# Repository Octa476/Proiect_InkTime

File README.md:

# Proiect_InkTime

Schematic, PCB design si 3D modeling pentru ceasul InkTime in cadrul proiectului de la materia TSC.

## Diagrama Bloc

Diagrama bloc a proietului (o varianta destul de minimala, dar suficienta pentru a intelege cum interactioneaza componentele intre ele) este prezenta in folder-ul root proiectului in varianta HTML si a fost realizata folosind [www.drawio.com](https://www.drawio.com/).

## BOM
Un Bills of Materials cu componentele folosite in cadrul acestui proiect.

### Componente active
 
| Component | Part Number | Package | Function | JLCPCB Part | Datasheet |
|-----------|------------|---------|----------|-------------|-----------|
| MCU | nRF52840-QIAA-R | aQFN73 (7x7) | Microcontroller + BLE + USB | [C190794](https://jlcpcb.com/partdetail/Nordic_Semicon-NRF52840_QIAA_R/C190794) | [Datasheet](https://infocenter.nordicsemi.com/pdf/nRF52840_PS_v1.8.pdf) |
| Charger / Power Path | BQ25180YBGR | DSBGA-8 | Li-Ion/LiPo charger with power path | [C3682423](https://jlcpcb.com/partdetail/TexasInstruments-BQ25180YBGR/C3682423) | [Datasheet](https://www.ti.com/lit/ds/symlink/bq25180.pdf) |
| Buck-Boost Regulator | RT6160AWSC | WLCSP-15 | 3.3V system rail regulator | [C7065276](https://jlcpcb.com/partdetail/Richtek_Tech-RT6160AWSC/C7065276) | [Datasheet](https://www.richtek.com/assets/product_file/RT6160A/DS6160A-05.pdf) |
| Fuel Gauge | MAX17048G+T10 | DFN-8 (2x2) | Battery SOC monitoring | [C2682616](https://jlcpcb.com/partdetail/AnalogDevices-MAX17048G_T10/C2682616) | [Datasheet](https://www.analog.com/media/en/technical-documentation/data-sheets/MAX17048-MAX17049.pdf) |
| Accelerometer | BMA421 | LGA-12 (2x2) | Step counting + motion wake | [C5242966](https://jlcpcb.com/partdetail/Bosch_Sensortec-BMA421/C5242966) | [Datasheet](https://www.bosch-sensortec.com/media/boschsensortec/downloads/datasheets/bst-bma421-ds004.pdf) |
| Haptic Driver | DRV2605LDGSR | VSSOP-10 | ERM motor driver with effects library | [C527464](https://jlcpcb.com/partdetail/TexasInstruments-DRV2605LDGSR/C527464) | [Datasheet](https://www.ti.com/lit/ds/symlink/drv2605l.pdf) |
| PFET (EPD power) | SI2301CDS | SOT-23 | E-paper display power gating | [C10487](https://jlcpcb.com/partdetail/Changjiang_Electronics_Tech_CJ-SI2301CDS/C10487) | [Datasheet](https://www.vishay.com/docs/68749/si2301cds.pdf) |
| USB ESD Protection | USBLC6-2SC6Y | SOT-23-6 | ESD protection on USB data lines | [C7519](https://jlcpcb.com/partdetail/Stmicroelectronics-USBLC6_2SC6Y/C7519) | [Datasheet](https://www.st.com/resource/en/datasheet/usblc6-2.pdf) |
 
### Conectori & Componente electromecanice
 
| Component | Part Number | Package | Function | JLCPCB Part | Datasheet |
|-----------|------------|---------|----------|-------------|-----------|
| FPC Connector (Display) | Molex 503480-2400 | 24-pin 0.5mm FPC | E-paper display FPC connection | [C2857160](https://jlcpcb.com/partdetail/Molex-5034802400/C2857160) | [Datasheet](https://www.molex.com/en-us/products/part-detail/5034802400) |
| USB Type-C Connector | KH-TYPE-C-16P | 16-pin SMD | USB charging + data | [C2765186](https://jlcpcb.com/partdetail/Kinghelm-KH_TYPE_C_16P/C2765186) | [Datasheet](https://datasheet.lcsc.com/lcsc/2012121836_Kinghelm-KH-TYPE-C-16P_C2765186.pdf) |
| Buttons (x3) | EVP-AKE31A | SMD tactile | Up / Down / Enter navigation | [C2845028](https://jlcpcb.com/partdetail/Panasonic-EVP_AKE31A/C2845028) | [Datasheet](https://industrial.panasonic.com/cdbs/www-data/pdf/ATV0000/ATV0000CE3.pdf) |
| SWD Debug Header | TC2030-IDC | Tag-Connect 6-pin | SWD programming + debug | - | [Datasheet](https://4donline.ihs.com/images/VipMasterIC/IC/TGCN/TGCN-S-A0008988129/TGCN-S-A0008988129-1.pdf?hkey=61A2E4C270F0397D049F8F05BD4F1054) |
| Antenna | 2450AT18B100E | SMD 3216 | 2.4 GHz BLE chip antenna | [C5179427](https://jlcpcb.com/partdetail/Johanson_Technology-2450AT18B100E/C5179427) | [Datasheet](https://www.johansontechnology.com/datasheets/2450AT18B100/2450AT18B100.pdf) |
 
### Componente Pasive
 
| Component | Value | Package | Qty | Function |
|-----------|-------|---------|-----|----------|
| Capacitors (EPD) | 1uF/50V | 0402 | 9 | E-paper driver capacitors |
| Capacitors (decoupling) | 100nF | 0201 | 5 | MCU + peripheral decoupling |
| Capacitors (crystal load) | 12pF | 0201 | 4 | 32MHz + 32.768kHz crystal loads |
| Capacitors (bulk) | 4.7uF | 0402 | 4 | MCU power rail bulk decoupling |
| Capacitors (charger) | 1uF | 0402 | 3 | BQ25180 CIN/CSYS/CBAT |
| Capacitors (power) | 22uF | 0402 | 2 | RT6160 input capacitors |
| Capacitors (USB) | 4.7uF | 0402 | 1 | DECUSB capacitor |
| Resistors (I2C pull-up) | 10k | 0201 | 2 | I2C SDA/SCL pull-ups |
| Resistors (USB CC) | 5.1k | 0201 | 2 | USB Type-C CC1/CC2 pull-downs |
| Inductor (DC/DC) | 10uH | 0402 | 1 | nRF52840 REG1 DC/DC inductor |
| Inductor (buck-boost) | 0.47uH | 2012 | 1 | RT6160 power stage inductor |
| Crystal | 32 MHz | 2016 | 1 | HFXO for MCU + radio |
| Crystal | 32.768 kHz | 3215 | 1 | LFXO for RTC timekeeping |
 
### Componente asamblate manual
 
| Component | Description | Datasheet |
|-----------|-------------|-----------|
| E-Paper Display | 1.54" 200x200 e-paper panel (connected via 24-pin FPC) | [Datasheet](https://www.tme.eu/Document/0ca57a8ffbcd57b5bca53252eb9d6ec3/WSH-12561.pdf)
| LiPo Battery | 3.7V / 250mAh lithium polymer cell | [Datasheet](https://www.tme.eu/Document/b9e12bf26ad0ba929a22ab5d58f022cd/AKY0106.pdf) |
| ERM Motor | Vibration motor (LCM1027B3605F, wire-soldered) | [Datasheet](https://www.mouser.com/pdfDocs/ProductOverview_DFRobot-FIT0774.pdf?srsltid=AfmBOorF7wbF3rhjcccF6FYMm4IWaUvm-yoIZHtvcCPKd2GPxZIuuKFv) |
| Case | 3D-printed case (SLS/MJF or FDM prototype) | [Soon](https://www.youtube.com/watch?v=xm3YgoEiEDc&list=RDxm3YgoEiEDc&start_radio=1) |

## Descrierea functionalitatii hardware

### **I2C**: LiPo Charger, DC/DC, IMU, Fuel Gauge, Haptic Driver;
### **SPI**: E-Paper Display Connector;

### Sheet1:
- **LiPo Charger** este folosit pentru a incarca bateria;
- **DC/DC** este un stabilizator de tensiune si este folosit pentru a oferi o tensiune stabila de 3V3 intregii placi;
- **IMU** este un accelerometru, fiind utilizat pentru determinarea acceleratiei pe cele 3 axe, numararea pasilor, etc;
- **nRF52840** este microcontroller-ul placutei si controleaza si orchestreaza intreaga functionalitate a acesteia;
- **SWD** - este mufa pentru conectorul de debug;

### Sheet2:
- **E-Paper Drive Circuit** este folosit pentru a controla display-ul si a oferii tensiuni de alimentare potrivite;
- **E-Paper Display Connector** - conectorul ce face legatura intre display si restul sistemului;
- **Fuel Gauge** este o componenta care indica nivelul de incarcare al bateriei;
- **USB C Connector** este mufa usb;
- **ESD Protection** este un modul ce protejeaza placuta de descarcarile elctrostatice ce pot aparea in utilizarea zilnica a ceasului;
- **Haptic Driver** este folosit pentru a controla vibratia shaker-ului;
- **Buttons** vor indeplini anumite functii in interfata cu utilizatorul (mai multe detalii in implementarea software);

## Descriere pini nRF52840 (randul de sus, sens invers trigonometric)

| Pin | Descriere |
|-----------|-------------|
| VDD | alimentarea la 3V3 |
| DCC | power regulation | 
| DEC4 | power regulation |
| VSS | GND |
| P0.31/AIN7-4 | nefolosit |
| P0.02/AIN0 | SCK - pinul de clock pentru protocolul SPI prin care comunica conectorul de display |
| P0.02/AIN0 | MOSI - master output slave in, folosit pentru comunicarea SPI |
| P1.15-12 | nefolosit |
| DEC2 | GND, power regulation |
| P1.12-11 | nefolosit |
| VDD | 3V3 |
| XC2, XC1 | pini pentru sursa de ceas X1 de 32MHz |
| DEC3 | GND |
| DEC6 | power regulation |
| VSS_PA | alimentare antena |
| ANT | pin folosit pentru legarea la antena |
| P0.10/NFC2 | pin folosit probabil pentru ca Fuel Gauge sa anunte microcontroller-ul cand tensiunea bateriei ajunse sa fie mai mica decat un prag anume |
| P0.09/NFC1 | nefolosit |
| DEC5 | GND, power regulation |
| P1.07-03 | nefolosit |
| P1.02 | buton down |
| P1.01 | controleaza tensiunea de alimentare a display-ului prin driver |
| SWDIO, SWDCLK | pini utilizati pentru depanarea si programarea microcontroller-ului |
| VDD | 3V3 |
| VSS_PAD | GND |
| P1.00 | SWO - pin utilizat pentru depanarea si programarea microcontroller-ului |
| P0.25-19 | nefolosit |
| P.18/RESET | maretul pin de reset |
| P0.17, P0.16, P0.15 | pini folositi pentru tranzactionarea cu display-ul |
| P0.13, P0.14| buton ent, buton up |
| D-, D+ | pini folositi la tranzactionarea datelor de la USB; folosesc tranmisie diferentiala |
| VBUS | alimentarea la 5V a unui USB |
| DEC3V3 | GND (ciudat putin, SoC interesant) |
| DCCH | nefolosit |
| VDDH, VDD | 3V3 |
| P0.12 | enable pentru driverul haptic |
| P0.11 | folosit pentru atentiona microcontroller-ul de posibile hazarde de alimentare; este controlar de Lipo Charger |
| P1.09 | nefolosit |
| P1.08, P0.08 | pini de intrerupere pentru modulul de IMU |
| P0.07, P0.06 | pini folositi de protocolul I2C |
| P0.05/AIN3 | chip select pentru display |
| P0.04/AIN2, P0.27, P0.26 | nefolosit |
| XL2, XL1 | pini pentru sursa de ceas X2 de 32KHz |
| DEC1 | GND, power regulation |

## Aspecte de design

- am ales sa realizez PCB-ul pe 4 straturi. Am un plan top, unul bottom, un plan de masa pe layer-ul de sub top si un plan de 3V3 pe layer-ul de deasupra lui bottom;
- am pozitionat antena in partea de jos a placii, langa butoane si am decupat straturile de cupru de sub aceasta;
- am folosit via in pad si am din aceasta cauza cateva erori pe care le-am acceptat deoarece era singura solutie viabila;
- am ales sa am un nivel de detaliu mediu in cadrul modelarii 3D a bateriei, display-ului si shaker-ului
- am conectat shaker-ul si bateria prin fire la test pad-urile asociate lor;
- am curbat conectorul flex al display-ului pentru a se potrivi in concectorul de pe PCB folosind comanda bend pentru metal sheets;
- am folosit niste inlocuitori pentru modelul 3D al unor piese, deoarece nu am putut identifica un model exact al footprint-ului din schematic sau footprint-ul nu era unul specificat tehnic (ex: PERFECT_0402, JUMPER_SJ, etc);
- am realilzat un exploded view vertical, in care sunt prezente piesele dezasamblate ale ceasului;
- am inclus cateva screenshot-uri de pe parcursul dezvolatarii proiectului in folderul Images;

## Observatii personale

Proiectul a fost extrem de muncitoresc si plin de frustrari din mai multe puncte de vedere. In primul rand, nu am fost "scoliti" in a utiliza la capacitate scazuta spre medie facilitatile de care dispune aplicatia Fusion Autodesk, fapt ce a dus la un loop aproape infinit de vizionat tutoriale si incercari repetate inutile de trage o curba in spatiu pentru desenarea firelor de legatura (un umil exemplu). Mi-as fi dorit ca laboratoarele sa prezinte mai in detaliu functionalitatile esentiale in realizarea proiectului si consider ca nu este o virtute faptul ca ne-am descurcat singuri, deoarece timpul pe care il avem este deja extrem de limitat (da, am invatat multe, pe cont propriu sau prin viu grai, dar ar fi fost mult mai usor sa fim instruiti macar putin mai mult).

Dupa aceasta critica constructiva, as dorii totusi sa felicit ideea de a propune un astfel de proiect. A fost un proces interesant de design, atat la nivel de PCB, cat si modelare 3D, si simt ca m-a ajutat sa ma dezvolt pe plan ingineresc. Am invatat sa ma descurc singur, sa incerc, m-am enervat de multe ori, dar intr-un final am reusit sa fixez un fir exact in pozitia in care imi doream.
Fun fact, am avut un bug in fusion care imi bloca coada de task-uri si ajunsesem sa am in jur de 240 de task-uri in processing, fapt ce imi bloca orice incercare de a exporta un fisier 3D. Din fericire, am rezolvat aceasta problema printr-o comanda text inteligenta.

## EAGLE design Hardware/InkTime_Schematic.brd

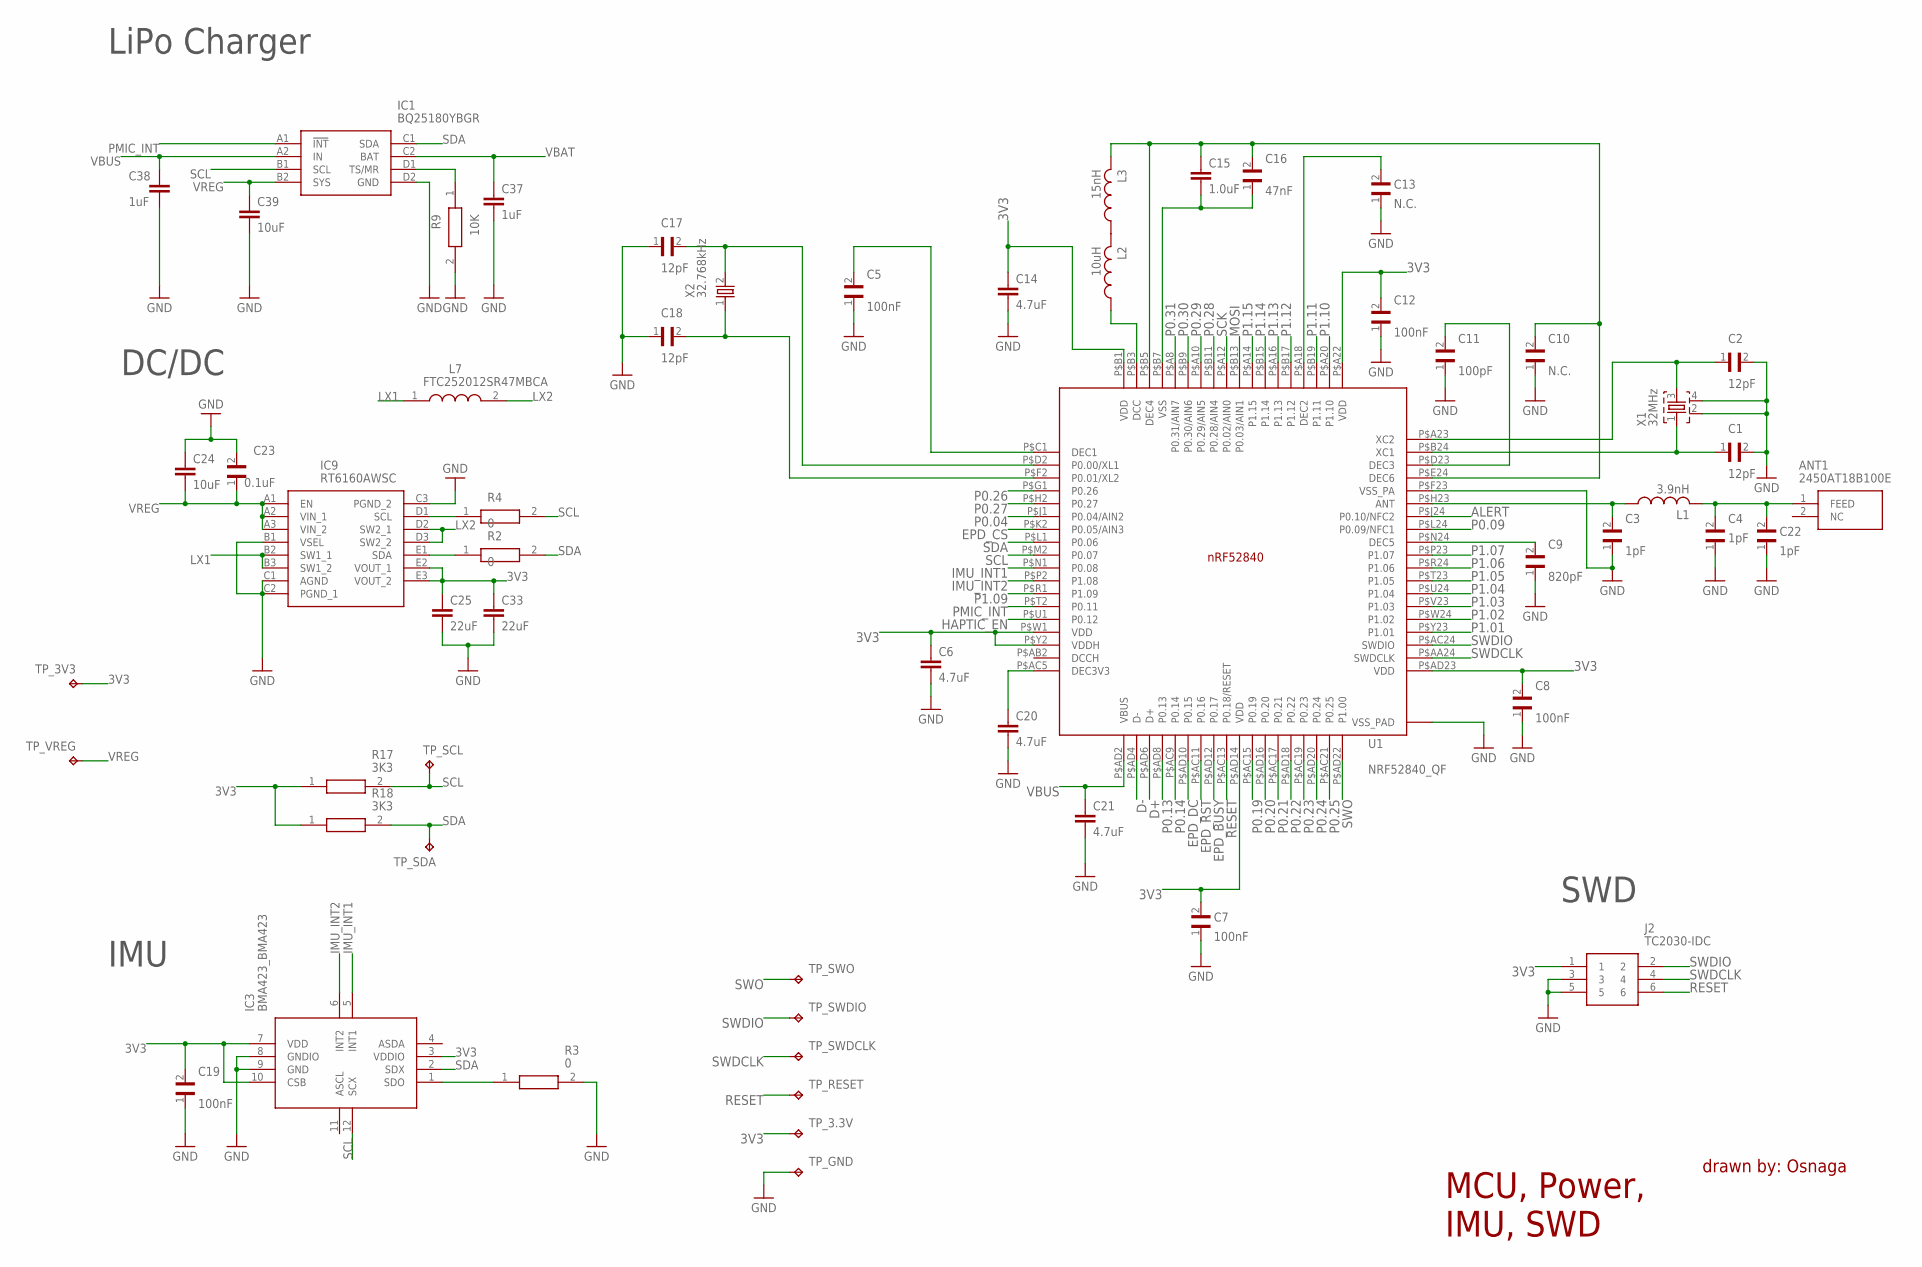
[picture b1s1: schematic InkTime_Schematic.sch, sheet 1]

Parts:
ANT1: 2450AT18B100E; 2450AT18B100E_ANTC3216X140N
C1, C2, C17, C18: 12pF; GRM011R60J152KE01L_2_CAPC0201X13N
C3, C4, C22: 1pF; GRM011R60J152KE01L_2_CAPC0201X13N
C5, C7, C8, C12, C19: 100nF; GRM011R60J152KE01L_2_CAPC0201X13N
C6, C14, C20, C21: 4.7uF; PERFECT_0402_0402
C9: 820pF; GRM011R60J152KE01L_2_CAPC0201X13N
C10, C13: N.C.; GRM011R60J152KE01L_2_CAPC0201X13N
C11: 100pF; GRM011R60J152KE01L_2_CAPC0201X13N
C15: 1.0uF; PERFECT_0402_0402
C16: 47nF; GRM011R60J152KE01L_2_CAPC0201X13N
C23: 0.1uF; GRM011R60J152KE01L_2_CAPC0201X13N
C24, C39: 10uF; PERFECT_0402_0402
C25, C33: 22uF; PERFECT_0402_0402
C37, C38: 1uF; PERFECT_0402_0402
IC1: BQ25180YBGR; BQ25180YBGR_BGA8C40P2X4_100X155X50
IC3: BMA423_BMA423
IC9: RT6160AWSC; RT6160AWSC_BGA15C40P3X5_140X230X60
J2: TC2030-IDC; TC2030-IDC_TC2030IDC
L1: 3.9nH; NORDIC_NRF_2_RESC0201_L
L2: 10uH; NORDIC_NRF_2_RESC0201_L
L3: 15nH; NORDIC_NRF_2_RESC0201_L
L7: FTC252012SR47MBCA; MLP2016SR47MT0S1_INDC2016X100N
R2, R3, R4: 0; CPF0201D7K68C1_0201
R9: 10K; CPF0201D7K68C1_0201
R17, R18: 3K3; CPF0201D7K68C1_0201
TP_3.3V, TP_3V3: HECTOR_WATCH_1_TPTP20R; HECTOR_WATCH_1_TP20R
TP_GND: HECTOR_WATCH_1_TPTP20R; HECTOR_WATCH_1_TP20R
TP_RESET: HECTOR_WATCH_1_TPTP20R; HECTOR_WATCH_1_TP20R
TP_SCL: HECTOR_WATCH_1_TPTP20R; HECTOR_WATCH_1_TP20R
TP_SDA: HECTOR_WATCH_1_TPTP20R; HECTOR_WATCH_1_TP20R
TP_SWDCLK: HECTOR_WATCH_1_TPTP20R; HECTOR_WATCH_1_TP20R
TP_SWDIO: HECTOR_WATCH_1_TPTP20R; HECTOR_WATCH_1_TP20R
TP_SWO: HECTOR_WATCH_1_TPTP20R; HECTOR_WATCH_1_TP20R
TP_VREG: HECTOR_WATCH_1_TPTP20R; HECTOR_WATCH_1_TP20R
U1: NRF52840_QF; NORDIC_NRF_4_AQFN50P700X700X85_HS-74N
X1: 32MHz; NORDIC_NRF_BT-XTAL_2016_N
X2: 32.768kHz; NORDIC_NRF_1_XTAL_3215_N

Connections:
3V3: C6.1, C7.2, C8.2, C12.2, C14.1, C19.2, C25.1, C33.1, IC3.3 (VDDIO), IC3.7 (VDD), IC3.10 (CSB), IC9.E2 (VOUT_1), IC9.E3 (VOUT_2), J2.1, R17.1, R18.1, TP_3.3V.TP, TP_3V3.TP, U1.P$A22 (VDD), U1.P$AD14 (VDD), U1.P$AD23 (VDD), U1.P$B1 (VDD), U1.P$W1 (VDD), U1.P$Y2 (VDDH); also elsewhere on the board
ALERT: U1.P$J24 (P0.10/NFC2); also elsewhere on the board
D+: U1.P$AD6 (D+); also elsewhere on the board
D-: U1.P$AD4 (D-); also elsewhere on the board
EPD_BUSY: U1.P$AD12 (P0.17); also elsewhere on the board
EPD_CS: U1.P$K2 (P0.05/AIN3); also elsewhere on the board
EPD_DC: U1.P$AD10 (P0.15); also elsewhere on the board
EPD_RST: U1.P$AC11 (P0.16); also elsewhere on the board
GND: C1.2, C2.2, C3.1, C4.1, C5.1, C6.2, C7.1, C8.1, C9.1, C10.1, C11.1, C12.1, C13.1, C14.2, C17.1, C18.1, C19.1, C20.2, C21.2, C22.1, C23.2, C24.1, C25.2, C33.2, C37.2, C38.2, C39.2, IC1.D2 (GND), IC3.8 (GNDIO), IC3.9 (GND), IC9.B1 (VSEL), IC9.C1 (AGND), IC9.C2 (PGND_1), IC9.C3 (PGND_2), J2.3, J2.5, R3.2, R9.2, TP_GND.TP, U1.P$74 (VSS_PAD), U1.P$75 (VSS_PAD), U1.P$76 (VSS_PAD), U1.P$77 (VSS_PAD), U1.P$78 (VSS_PAD), U1.P$79 (VSS_PAD), U1.P$80 (VSS_PAD), U1.P$81 (VSS_PAD), U1.P$82 (VSS_PAD), U1.P$83 (VSS_PAD), U1.P$84 (VSS_PAD), U1.P$85 (VSS_PAD), U1.P$86 (VSS_PAD), U1.P$87 (VSS_PAD), U1.P$88 (VSS_PAD), U1.P$89 (VSS_PAD), U1.P$90 (VSS_PAD), U1.P$F23 (VSS_PA), X1.2, X1.4; also elsewhere on the board
HAPTIC_EN: U1.P$U1 (P0.12); also elsewhere on the board
IMU_INT1: IC3.5 (INT1), U1.P$N1 (P0.08)
IMU_INT2: IC3.6 (INT2), U1.P$P2 (P1.08)
LX1: IC9.B2 (SW1_1), IC9.B3 (SW1_2), L7.1
LX2: IC9.D2 (SW2_1), IC9.D3 (SW2_2), L7.2
MOSI: U1.P$B13 (P0.03/AIN1); also elsewhere on the board
unnamed: IC9.D1 (SCL), R4.1
unnamed: IC9.E1 (SDA), R2.1
unnamed: C20.1, U1.P$AC5 (DEC3V3)
unnamed: C5.2, U1.P$C1 (DEC1)
unnamed: IC3.1 (SDO), R3.1
unnamed: IC1.D1 (TS/MR), R9.1
unnamed: C17.2, U1.P$D2 (P0.00/XL1), X2.2
unnamed: L2.2, L3.1
unnamed: L2.1, U1.P$B3 (DCC)
unnamed: C18.2, U1.P$F2 (P0.01/XL2), X2.1
unnamed: C15.2, C16.1, U1.P$B7 (VSS)
unnamed: C11.2, U1.P$D23 (DEC3)
unnamed: C2.1, U1.P$A23 (XC2), X1.3
unnamed: C1.1, U1.P$B24 (XC1), X1.1
unnamed: C3.2, L1.1, U1.P$H23 (ANT)
unnamed: ANT1.1 (FEED), C4.2, C22.2, L1.2
unnamed: C13.2, U1.P$A18 (DEC2)
unnamed: C9.2, U1.P$N24 (DEC5)
unnamed: C10.2, C15.1, C16.2, L3.2, U1.P$B5 (DEC4), U1.P$E24 (DEC6)
P0.04: U1.P$J1 (P0.04/AIN2)
P0.09: U1.P$L24 (P0.09/NFC1)
P0.13: U1.P$AD8 (P0.13); also elsewhere on the board
P0.14: U1.P$AC9 (P0.14); also elsewhere on the board
P0.19: U1.P$AC15 (P0.19)
P0.20: U1.P$AD16 (P0.20)
P0.21: U1.P$AC17 (P0.21)
P0.22: U1.P$AD18 (P0.22)
P0.23: U1.P$AC19 (P0.23)
P0.24: U1.P$AD20 (P0.24)
P0.25: U1.P$AC21 (P0.25)
P0.26: U1.P$G1 (P0.26)
P0.27: U1.P$H2 (P0.27)
P0.28: U1.P$B11 (P0.28/AIN4)
P0.29: U1.P$A10 (P0.29/AIN5)
P0.30: U1.P$B9 (P0.30/AIN6)
P0.31: U1.P$A8 (P0.31/AIN7)
P1.01: U1.P$Y23 (P1.01); also elsewhere on the board
P1.02: U1.P$W24 (P1.02); also elsewhere on the board
P1.03: U1.P$V23 (P1.03)
P1.04: U1.P$U24 (P1.04)
P1.05: U1.P$T23 (P1.05)
P1.06: U1.P$R24 (P1.06)
P1.07: U1.P$P23 (P1.07)
P1.09: U1.P$R1 (P1.09)
P1.10: U1.P$A20 (P1.10)
P1.11: U1.P$B19 (P1.11)
P1.12: U1.P$B17 (P1.12)
P1.13: U1.P$A16 (P1.13)
P1.14: U1.P$B15 (P1.14)
P1.15: U1.P$A14 (P1.15)
PMIC_INT: IC1.A1 (!INT), U1.P$T2 (P0.11)
RESET: J2.6, TP_RESET.TP, U1.P$AC13 (P0.18/RESET)
SCK: U1.P$A12 (P0.02/AIN0); also elsewhere on the board
SCL: IC1.B1 (SCL), IC3.12 (SCX), R4.2, R17.2, TP_SCL.TP, U1.P$M2 (P0.07); also elsewhere on the board
SDA: IC1.C1 (SDA), IC3.2 (SDX), R2.2, R18.2, TP_SDA.TP, U1.P$L1 (P0.06); also elsewhere on the board
SWDCLK: J2.4, TP_SWDCLK.TP, U1.P$AA24 (SWDCLK)
SWDIO: J2.2, TP_SWDIO.TP, U1.P$AC24 (SWDIO)
SWO: TP_SWO.TP, U1.P$AD22 (P1.00)
VBAT: C37.1, IC1.C2 (BAT); also elsewhere on the board
VBUS: C21.1, C38.1, IC1.A2 (IN), U1.P$AD2 (VBUS); also elsewhere on the board
VREG: C23.1, C24.2, C39.1, IC1.B2 (SYS), IC9.A1 (EN), IC9.A2 (VIN_1), IC9.A3 (VIN_2), TP_VREG.TP

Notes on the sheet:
LiPo Charger
DC/DC
IMU
MCU, Power, IMU, SWD
drawn by: Osnaga
SWD

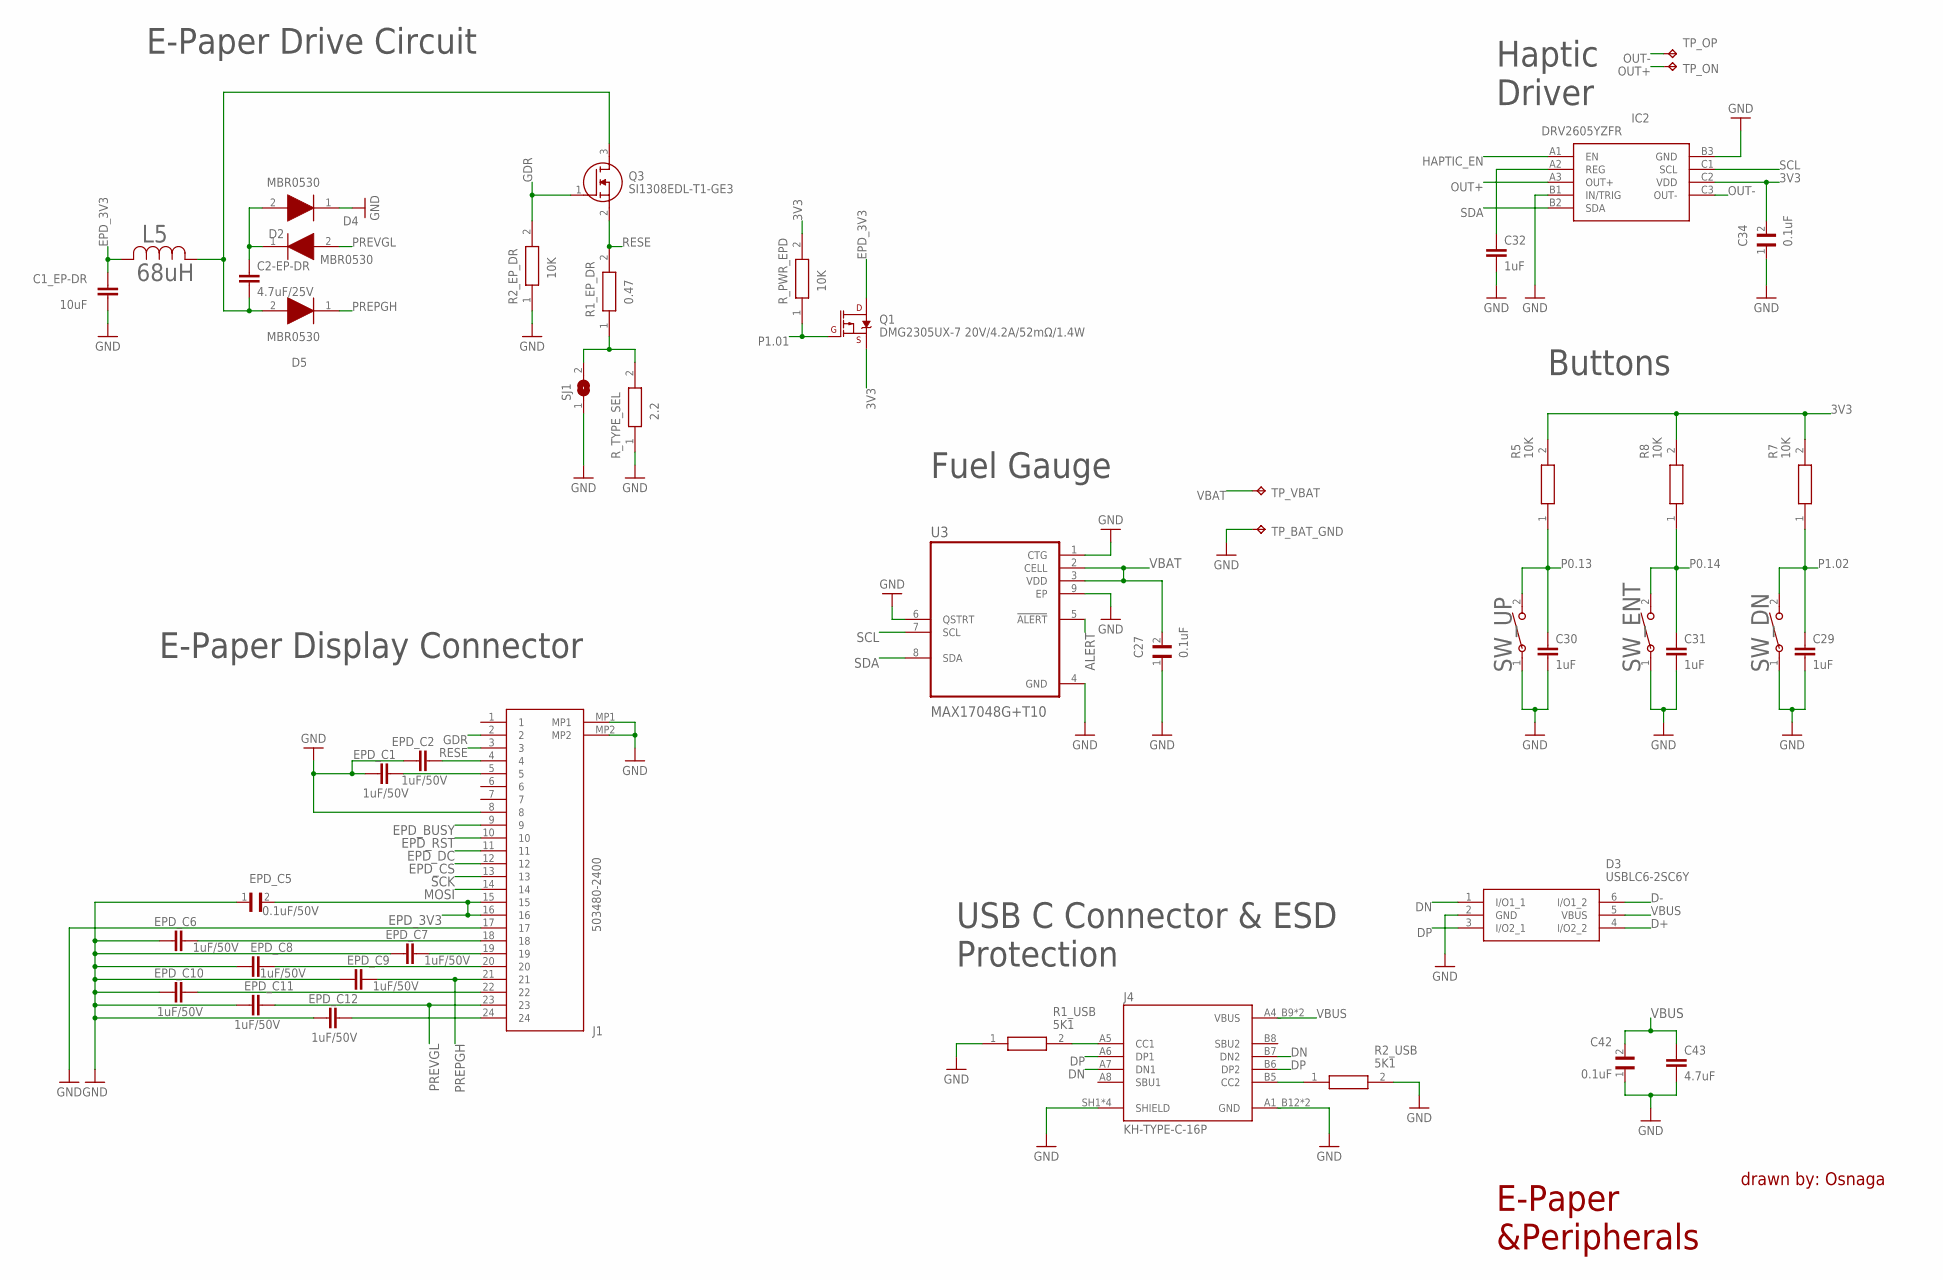
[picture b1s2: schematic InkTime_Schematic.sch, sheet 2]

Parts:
C1_EP-DR: 10uF; PERFECT_0402_0402
C2-EP-DR: 4.7uF/25V; PERFECT_0402_0402
C27, C34, C42: 0.1uF; GRM011R60J152KE01L_2_CAPC0201X13N
C29, C30, C31, C32: 1uF; PERFECT_0402_0402
C43: 4.7uF; PERFECT_0402_0402
D2, D4, D5: MBR0530; ESP32_C6_LIBRARY_5_SOD3716X135N
D3: USBLC6-2SC6Y; ESP32_C6_LIBRARY_3_SOT95P280X145-6N
EPD_C1, EPD_C2, EPD_C6, EPD_C7, EPD_C8, EPD_C9, EPD_C10, EPD_C11, EPD_C12: 1uF/50V; PERFECT_0402_0402
EPD_C5: 0.1uF/50V; GRM011R60J152KE01L_2_CAPC0201X13N
IC2: DRV2605YZFR; DRV2605YZFR_BGA9C50P3X3_144X144X62
J1: 503480-2400; 503480-2400_5034802400
J4: KH-TYPE-C-16P; KH-TYPE-C-16P_KINGHELM_KH-TYPE-C-16P
L5: 68uH; ESP32_C6_LIBRARY_2_IND_4828-WE-TPC_WRE
Q1: DMG2305UX-7 20V/4.2A/52mΩ/1.4W; ESP32_C6_LIBRARY_4_ESP32_C6_LIBRARY_4_ESP32_C6_LIBRARY_4_ES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
Q3: SI1308EDL-T1-GE3; ESP32_C6_LIBRARY_6_SOT65P210X110-3N
R1_EP_DR: 0.47; CPF0201D7K68C1_0201
R1_USB, R2_USB: 5K1; CPF0201D7K68C1_0201
R2_EP_DR, R5, R7, R8: 10K; CPF0201D7K68C1_0201
R_PWR_EPD: 10K; CPF0201D7K68C1_0201
R_TYPE_SEL: 2.2; CPF0201D7K68C1_0201
SJ1: ESP32_C6_LIBRARY_7_JUMPER_SJ
SW_DN: 2025-10-22_07-23-44_LIBRARY_EVP-AKE31ASW_EVP-AKE3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; 2025-10-22_07-23-44_LIBRARY_SW_EVP-AKE31A_PAN
SW_ENT: 2025-10-22_07-23-44_LIBRARY_EVP-AKE31ASW_EVP-AKE3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; 2025-10-22_07-23-44_LIBRARY_SW_EVP-AKE31A_PAN
SW_UP: 2025-10-22_07-23-44_LIBRARY_EVP-AKE31ASW_EVP-AKE3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; 2025-10-22_07-23-44_LIBRARY_SW_EVP-AKE31A_PAN
TP_BAT_GND: HECTOR_WATCH_1_TPTP20R; HECTOR_WATCH_1_TP20R
TP_ON: HECTOR_WATCH_1_TPTP20R; HECTOR_WATCH_1_TP20R
TP_OP: HECTOR_WATCH_1_TPTP20R; HECTOR_WATCH_1_TP20R
TP_VBAT: HECTOR_WATCH_1_TPTP20R; HECTOR_WATCH_1_TP20R
U3: MAX17048G+T10; ESP32_C6_LIBRARY_SON50P200X200X80-9N

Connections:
3V3: C34.2, IC2.C2 (VDD), Q1.2 (S), R5.2, R7.2, R8.2, R_PWR_EPD.2; also elsewhere on the board
ALERT: U3.5 (!ALERT); also elsewhere on the board
D+: D3.4 (I/O2_2); also elsewhere on the board
D-: D3.6 (I/O1_2); also elsewhere on the board
DN: D3.1 (I/O1_1), J4.A7 (DN1), J4.B7 (DN2)
DP: D3.3 (I/O2_1), J4.A6 (DP1), J4.B6 (DP2)
EPD_3V3: C1_EP-DR.1, EPD_C5.2, J1.15, J1.16, L5.2, Q1.3 (D)
EPD_BUSY: J1.9; also elsewhere on the board
EPD_CS: J1.12; also elsewhere on the board
EPD_DC: J1.11; also elsewhere on the board
EPD_RST: J1.10; also elsewhere on the board
GDR: J1.2, Q3.1 (G), R2_EP_DR.2
GND: C1_EP-DR.2, C27.1, C29.2, C30.2, C31.2, C32.2, C34.1, C42.1, C43.2, D3.2 (GND), D4.1 (K), EPD_C1.1, EPD_C2.1, EPD_C5.1, EPD_C6.1, EPD_C7.1, EPD_C8.1, EPD_C9.1, EPD_C10.1, EPD_C11.1, EPD_C12.1, IC2.B1 (IN/TRIG), IC2.B3 (GND), J1.8, J1.17, J1.MP1, J1.MP2, J4.A1_B12 (GND), J4.A12_B1 (GND), J4.SH1 (SHIELD), J4.SH2 (SHIELD), J4.SH3 (SHIELD), J4.SH4 (SHIELD), R1_USB.1, R2_EP_DR.1, R2_USB.2, R_TYPE_SEL.1, SJ1.1, SW_DN.1, SW_ENT.1, SW_UP.1, TP_BAT_GND.TP, U3.1 (CTG), U3.4 (GND), U3.6 (QSTRT), U3.9 (EP); also elsewhere on the board
HAPTIC_EN: IC2.A1 (EN); also elsewhere on the board
MOSI: J1.14; also elsewhere on the board
unnamed: EPD_C6.2, J1.18
unnamed: EPD_C7.2, J1.19
unnamed: EPD_C8.2, J1.20
unnamed: J4.B5 (CC2), R2_USB.1
unnamed: EPD_C10.2, J1.22
unnamed: EPD_C2.2, J1.4
unnamed: EPD_C1.2, J1.5
unnamed: EPD_C12.2, J1.24
unnamed: R1_EP_DR.1, R_TYPE_SEL.2, SJ1.2
unnamed: C2-EP-DR.2, D5.2 (A), L5.1, Q3.3 (D)
unnamed: J4.A5 (CC1), R1_USB.2
unnamed: C2-EP-DR.1, D2.1 (K), D4.2 (A)
unnamed: C32.1, IC2.A2 (REG)
OUT+: IC2.A3 (OUT+), TP_ON.TP
OUT-: IC2.C3 (OUT-), TP_OP.TP
P0.13: C30.1, R5.1, SW_UP.2; also elsewhere on the board
P0.14: C31.1, R8.1, SW_ENT.2; also elsewhere on the board
P1.01: Q1.1 (G), R_PWR_EPD.1; also elsewhere on the board
P1.02: C29.1, R7.1, SW_DN.2; also elsewhere on the board
PREPGH: D5.1 (K), EPD_C9.2, J1.21
PREVGL: D2.2 (A), EPD_C11.2, J1.23
RESE: J1.3, Q3.2 (S), R1_EP_DR.2
SCK: J1.13; also elsewhere on the board
SCL: IC2.C1 (SCL), U3.7 (SCL); also elsewhere on the board
SDA: IC2.B2 (SDA), U3.8 (SDA); also elsewhere on the board
VBAT: C27.2, TP_VBAT.TP, U3.2 (CELL), U3.3 (VDD); also elsewhere on the board
VBUS: C42.2, C43.1, D3.5 (VBUS), J4.A4_B9 (VBUS), J4.A9_B4 (VBUS); also elsewhere on the board

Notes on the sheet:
E-Paper Drive Circuit
Fuel Gauge
E-Paper Display Connector
USB C Connector & ESD Protection
Buttons
Haptic Driver
E-Paper &Peripherals
drawn by: Osnaga

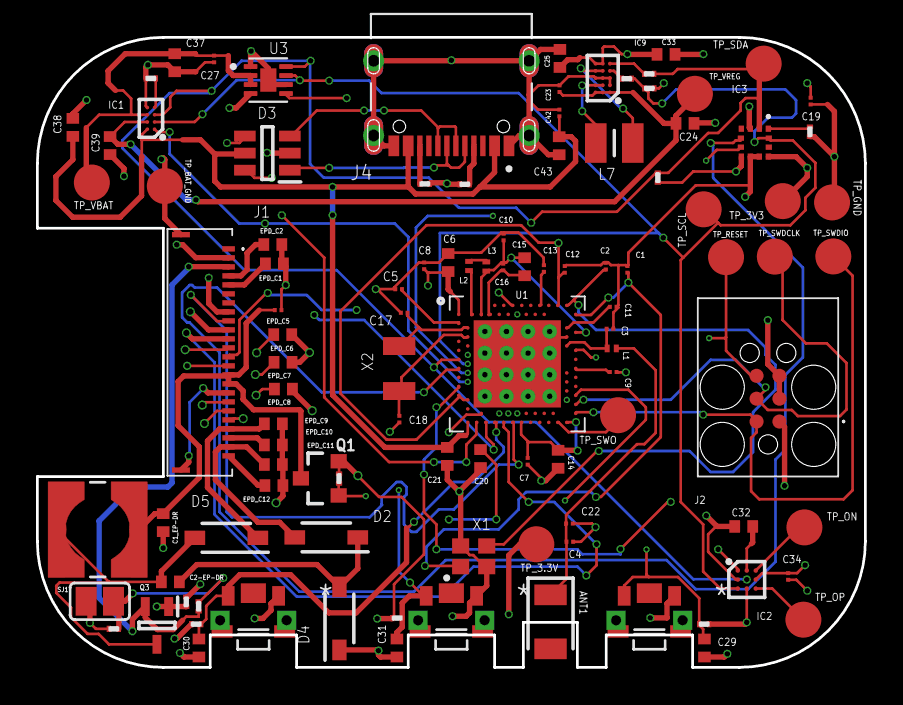
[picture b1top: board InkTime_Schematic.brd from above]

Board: 4 copper layers, 46.0 x 35.0 mm, 105 parts (0 on the bottom side), 71 nets.

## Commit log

2026-03-25 Prima incercare the schematic
2026-04-06 Finished the schematic and the PCB
2026-04-09 Finished the 3D design and exploded 3D view
2026-04-09 Am adaugat fisiere de manufacturing
2026-04-09 Am adaugat un README rough
2026-04-10 Am adaugat o poza a produsului
2026-04-18 Fixed the schematic and the pcb
2026-04-18 Added .pdf schematic and renamed .fbrb file
2026-04-18 Added new manufacturing folder
2026-04-18 Repaired silkscreen
2026-04-18 Added Images, updated mechanical
2026-04-18 Updated README, some work still unfinished
2026-04-19 Refined the README

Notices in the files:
parts and their libraries:
COPYRIGHT: Copyright (C) 2024 Ultra Librarian. All rights reserved.
COPYRIGHT: Copyright (C) 2025 Ultra Librarian. All rights reserved.
